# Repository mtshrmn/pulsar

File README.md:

# Pulsar - PulseAudio Volume Mixer

## Hardware Wiring

schematics will be added once everything is done and tested

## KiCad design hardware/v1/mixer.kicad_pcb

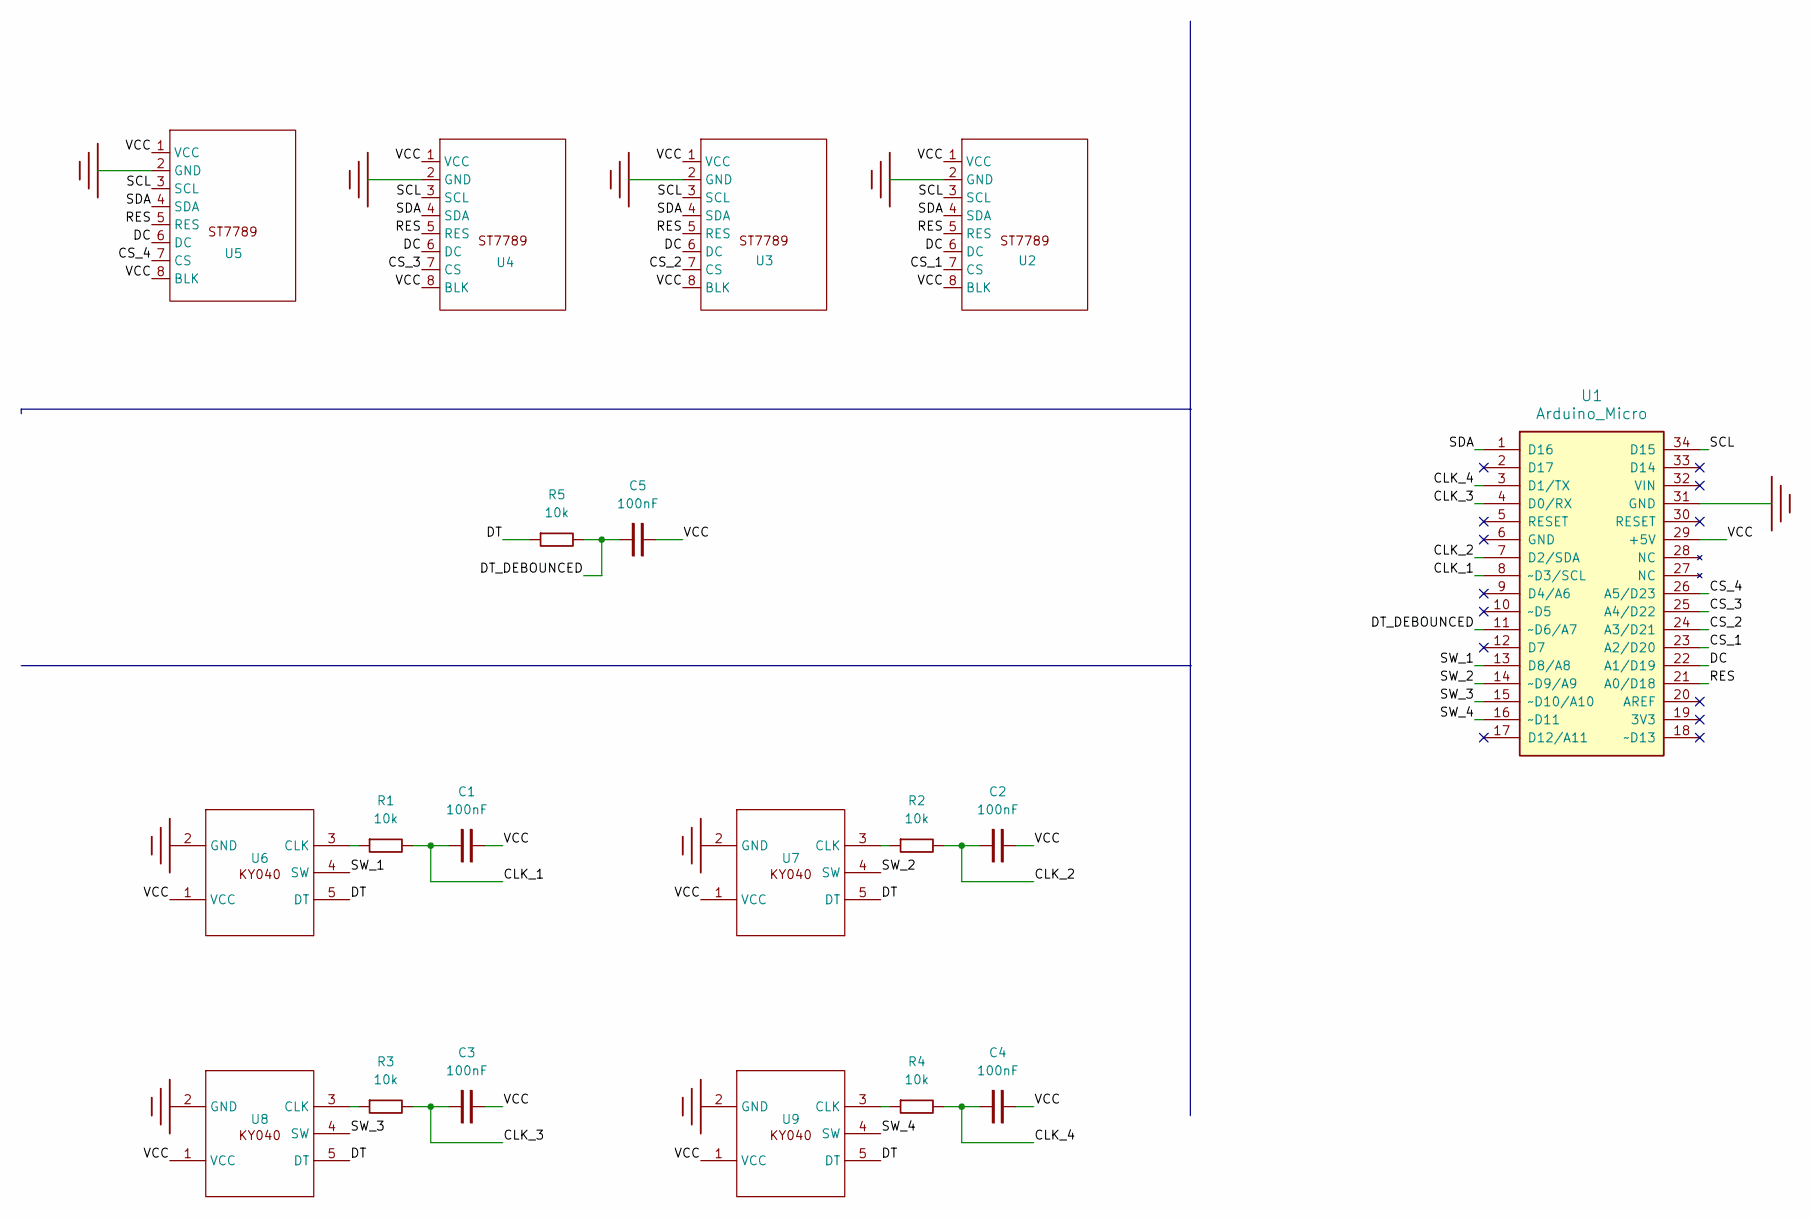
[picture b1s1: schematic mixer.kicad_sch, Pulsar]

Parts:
C1, C2, C3, C4, C5: 100nF; Mylar_Capacitor
R1, R2, R3, R4, R5: 10k; R_Axial_DIN0204_L3.6mm_D1.6mm_P5.08mm_Horizontal
U1: Arduino_Micro
U2, U3, U4, U5: ST7780_1_69
U6, U7, U8, U9: KY-040-PORT

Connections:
/CLK_1: C1.1, R1.2, U1.8 (~D3/SCL)
/CLK_2: C2.1, R2.2, U1.7 (D2/SDA)
/CLK_3: C3.1, R3.2, U1.4 (D0/RX)
/CLK_4: C4.1, R4.2, U1.3 (D1/TX)
/CS_1: U1.23 (A2/D20), U2.7 (CS)
/CS_2: U1.24 (A3/D21), U3.7 (CS)
/CS_3: U1.25 (A4/D22), U4.7 (CS)
/CS_4: U1.26 (A5/D23), U5.7 (CS)
/DC: U1.22 (A1/D19), U2.6 (DC), U3.6 (DC), U4.6 (DC), U5.6 (DC)
/DT: R5.1, U6.5 (DT), U7.5 (DT), U8.5 (DT), U9.5 (DT)
/DT_DEBOUNCED: C5.1, R5.2, U1.11 (~D6/A7)
/RES: U1.21 (A0/D18), U2.5 (RES), U3.5 (RES), U4.5 (RES), U5.5 (RES)
/SCL: U1.34 (D15), U2.3 (SCL), U3.3 (SCL), U4.3 (SCL), U5.3 (SCL)
/SDA: U1.1 (D16), U2.4 (SDA), U3.4 (SDA), U4.4 (SDA), U5.4 (SDA)
/SW_1: U1.13 (D8/A8), U6.4 (SW)
/SW_2: U1.14 (~D9/A9), U7.4 (SW)
/SW_3: U1.15 (~D10/A10), U8.4 (SW)
/SW_4: U1.16 (~D11), U9.4 (SW)
/VCC: C1.2, C2.2, C3.2, C4.2, C5.2, U1.29 (+5V), U2.1 (VCC), U2.8 (BLK), U3.1 (VCC), U3.8 (BLK), U4.1 (VCC), U4.8 (BLK), U5.1 (VCC), U5.8 (BLK), U6.1 (VCC), U7.1 (VCC), U8.1 (VCC), U9.1 (VCC)
unnamed: R1.1, U6.3 (CLK)
unnamed: R2.1, U7.3 (CLK)
unnamed: R3.1, U8.3 (CLK)
unnamed: R4.1, U9.3 (CLK)
P,E: U1.31 (GND), U2.2 (GND), U3.2 (GND), U4.2 (GND), U5.2 (GND), U6.2 (GND), U7.2 (GND), U8.2 (GND), U9.2 (GND)

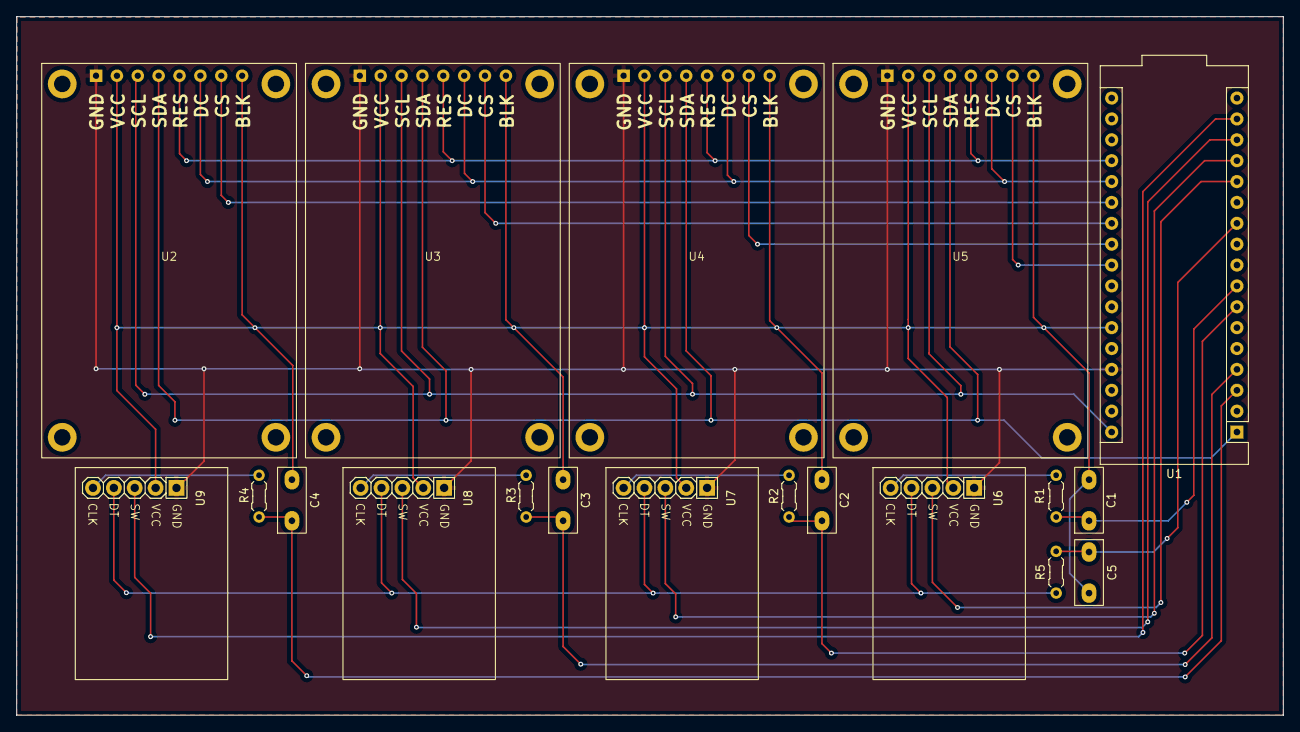
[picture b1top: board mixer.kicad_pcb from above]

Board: 2 copper layers, 154.2 x 85.0 mm, 19 parts (0 on the bottom side), 24 nets.

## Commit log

2025-03-05 modify CFLAGS to decrease file size
2025-03-08 gitignore .cache
2025-03-08 read entire range of potentiometer data
2025-03-08 implement minimal support for st7789 driver
2025-03-09 optimize write speed to st7789 memory
2025-03-09 implement drawing filled circles
2025-03-13 restructure entire project
2025-03-13 rename daemon.c to main.c
2025-03-13 fix daemon's make clean
2025-03-13 add simple connection to device via hidapi
2025-06-01 fix hid endpoints and add support for bulk
2025-06-01 rewrite daemon with libusb
2025-06-05 support transfer and render of images over bulk
2025-06-05 remove escalated privileges from daemon
    updated uvdev rules to allow device instead.
2025-06-06 add file and func name to logs
2025-06-06 add foundation for pulseaudio
2025-06-06 use NULL instead of 0 in pointer check
2025-06-06 send data to dev on sink inputs change
2025-06-07 restructure sink-input housekeeping
2025-06-07 add volume information to sink inputs
2025-06-25 add libusb event polling in mainloop
2025-07-13 quick and dirty poc of volume control
2025-08-09 wip: start write of daemon
2025-09-17 finish rewriting events/callbacks infrastructure
2025-09-17 move common definitions into protocol.h
2025-09-19 fix underlying daemon design and add hid methods
2025-09-19 dont run daemon if device is closed
2025-09-20 remove unused daemon retrying mechanism
2025-09-20 followup: remove unused retval in mainloop setup
2025-09-28 finish rewriting daemon
    this includes:
    - switching to single-threaded daemon.
    - creating a ring buffer for hid out reports.
    - including handshake of device with daemon on out reports.
    - implementing relevant pulseaudio events.
    - switching to dark theme on device.
2025-09-29 fix issue where sometimes icon isn't being drawn
2025-09-30 add volume control with rotary encoder
2025-09-30 fix: ignore invalid sink-index volume control
2025-09-30 tidy report handling from device
2025-10-01 handle case where num sinks > num displays
2025-10-01 remove opaque definitions from sinkctl header
2025-10-01 dont panic when removing invalid sink index from sink queue
2025-10-01 remove unused adc support
2025-10-01 add blocking hid enqueuing to prevent out-of-sync screen clearing
2025-10-03 add multi display support in device
2025-10-03 bugfix: enable interrupts after isr
2025-10-03 add readme with temporary wiring diagram
2025-10-04 cleanup dev descriptors struct
2025-10-11 rename project to `pulsar`
2025-10-19 remove software rotary encoder debouncing
    use hardware debouncing with RC
2025-10-24 fix some issues and update ports
2025-10-25 speed up tft drawing for parallel screens
2025-10-25 dont inline spi_transfer
2025-10-25 add support for louder than 100% volume
2025-11-12 update hardware schematics in readme
2025-11-23 add ISR handlers
2025-11-23 add untested hardware schematics (v1)
2025-12-07 fix dumb code
2025-12-07 clean up code
2025-12-11 handle phantom hid report(?) and arith-overflows
2025-12-12 add stricter CFLAGS for daemon
2025-12-12 fix warnings from stricter flags
2025-12-12 rename dev files to lowercase
2026-02-24 handle system suspension and resume
2026-02-24 fix usb device opening flow - return on success
2026-02-24 add indication for incomplete quadrant on device
2026-02-24 fix wrong command naming in st7789 init sequence
2026-02-25 try manualy opening device once before giving up
2026-02-27 dont wait for events without trying opening device
2026-02-27 revert latest commit
    this reverts commit 771dd0cb9e65fe20ef3273f837efb441362960a2.
    which removes waiting on a libusb event.
    sometimes there's a dangling libusb event that needs waited on.
2026-02-27 reduce libusb event wait timeout from 5s to 1s
2026-02-27 suspend/resume displays when host is suspended/resumed
2026-02-27 cleanup mixer code
2026-05-14 add support for pipewire-pulse
